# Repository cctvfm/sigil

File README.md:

# sigil
An ultra-compact contact mic with integrated phantom-powered JFET pre-amp

https://www.cctv.fm/product-page/sigil-transducer-diy-contact-mic-kit
cctv.fm/sigil

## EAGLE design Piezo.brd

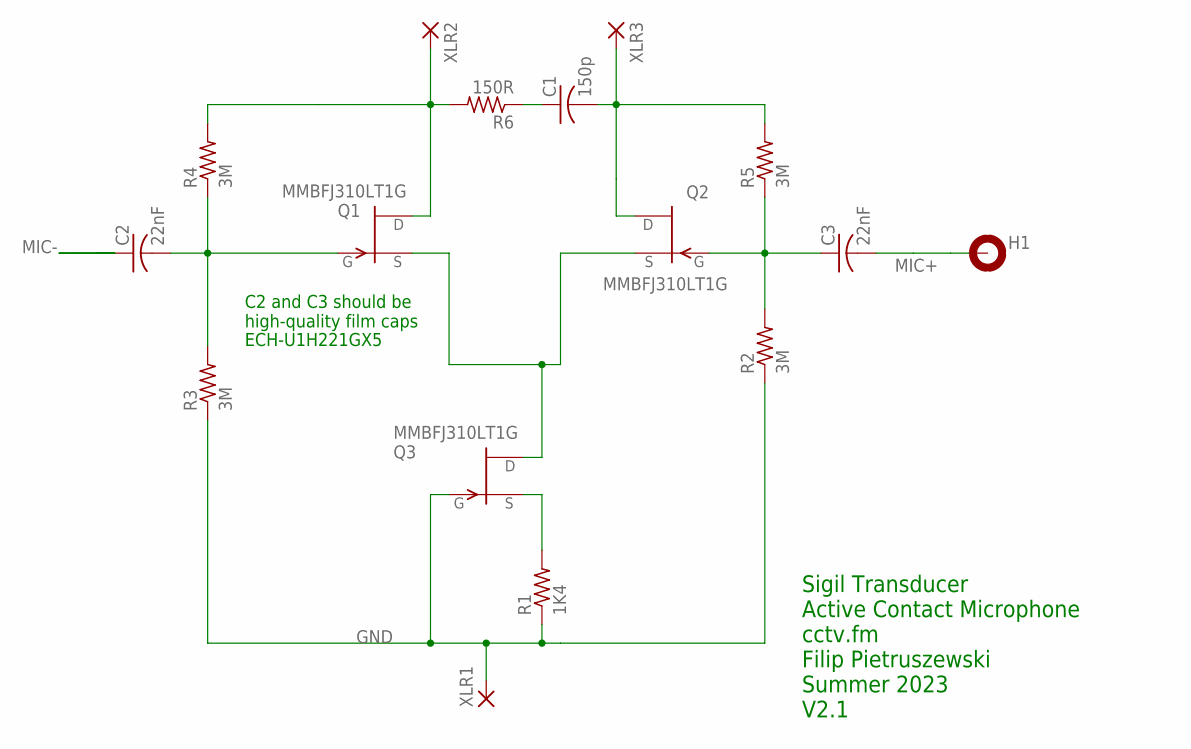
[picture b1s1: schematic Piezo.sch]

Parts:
C1: 150p; C0805
C2, C3: 22nF; C1206
H1: MOUNT-PAD-ROUND3.6; 3,6-PAD
Q1, Q2, Q3: MMBFJ310LT1G; SOT23
R1: 1K4; R0805
R2, R3, R4, R5: 3M; R0805
R6: 150R; R0805
XLR1, XLR2, XLR3: DNP; SMD2,54-5,08

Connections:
GND: Q3.3 (G), R1.1, R2.1, R3.1, XLR1.1
MIC+: C3.2, H1.B3,6
MIC-: C2.1
unnamed: Q1.2 (S), Q2.2 (S), Q3.1 (D)
unnamed: C2.2, Q1.3 (G), R3.2, R4.1
unnamed: C3.1, Q2.3 (G), R2.2, R5.1
unnamed: Q1.1 (D), R4.2, R6.2, XLR2.1
unnamed: Q3.2 (S), R1.2
unnamed: C1.1, R6.1
unnamed: C1.2, Q2.1 (D), R5.2, XLR3.1

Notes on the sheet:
ECH-U1H221GX5
C2 and C3 should be high-quality film caps
Sigil Transducer Active Contact Microphone cctv.fm Filip Pietruszewski Summer 2023 V2.1

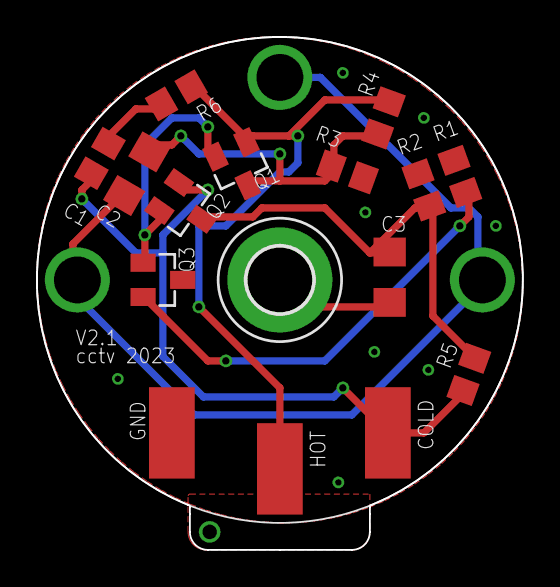
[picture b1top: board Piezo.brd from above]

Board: 2 copper layers, 27.0 x 28.5 mm, 16 parts (0 on the bottom side), 9 nets.

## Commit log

2023-08-03 Add files via upload
    Initial Upload
